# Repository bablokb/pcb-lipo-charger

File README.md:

A small LiPo Charger using the MCP73831 and the XB6166IS
========================================================

Here are the KiCAD (v6) design-files for a small LiPo charger.
The charger supports charging with an attached load.

The charging IC is the MCP73831T-2ACI/OT. For details, see the
schematic.

For battery protection, the XB6166IS from XySemi is used.
Overcurrent detection kicks in at about 900mA, so this is
not a charger for high loads.

The charge curve below shows both phases: constant current at
the beginning and constant voltage after reaching the cutoff
voltage. Charge termination is at 15mA.

Schematic
---------

Layout
------

3D-Views
--------

License
-------

[![CC BY-SA 4.0][cc-by-sa-shield]][cc-by-sa]

This work is licensed under a
[Creative Commons Attribution-ShareAlike 4.0 International
License][cc-by-sa].

[![CC BY-SA 4.0][cc-by-sa-image]][cc-by-sa]

[cc-by-sa]: http://creativecommons.org/licenses/by-sa/4.0/
[cc-by-sa-image]: https://licensebuttons.net/l/by-sa/4.0/88x31.png
[cc-by-sa-shield]:
https://img.shields.io/badge/License-CC%20BY--SA%204.0-lightgrey.svg

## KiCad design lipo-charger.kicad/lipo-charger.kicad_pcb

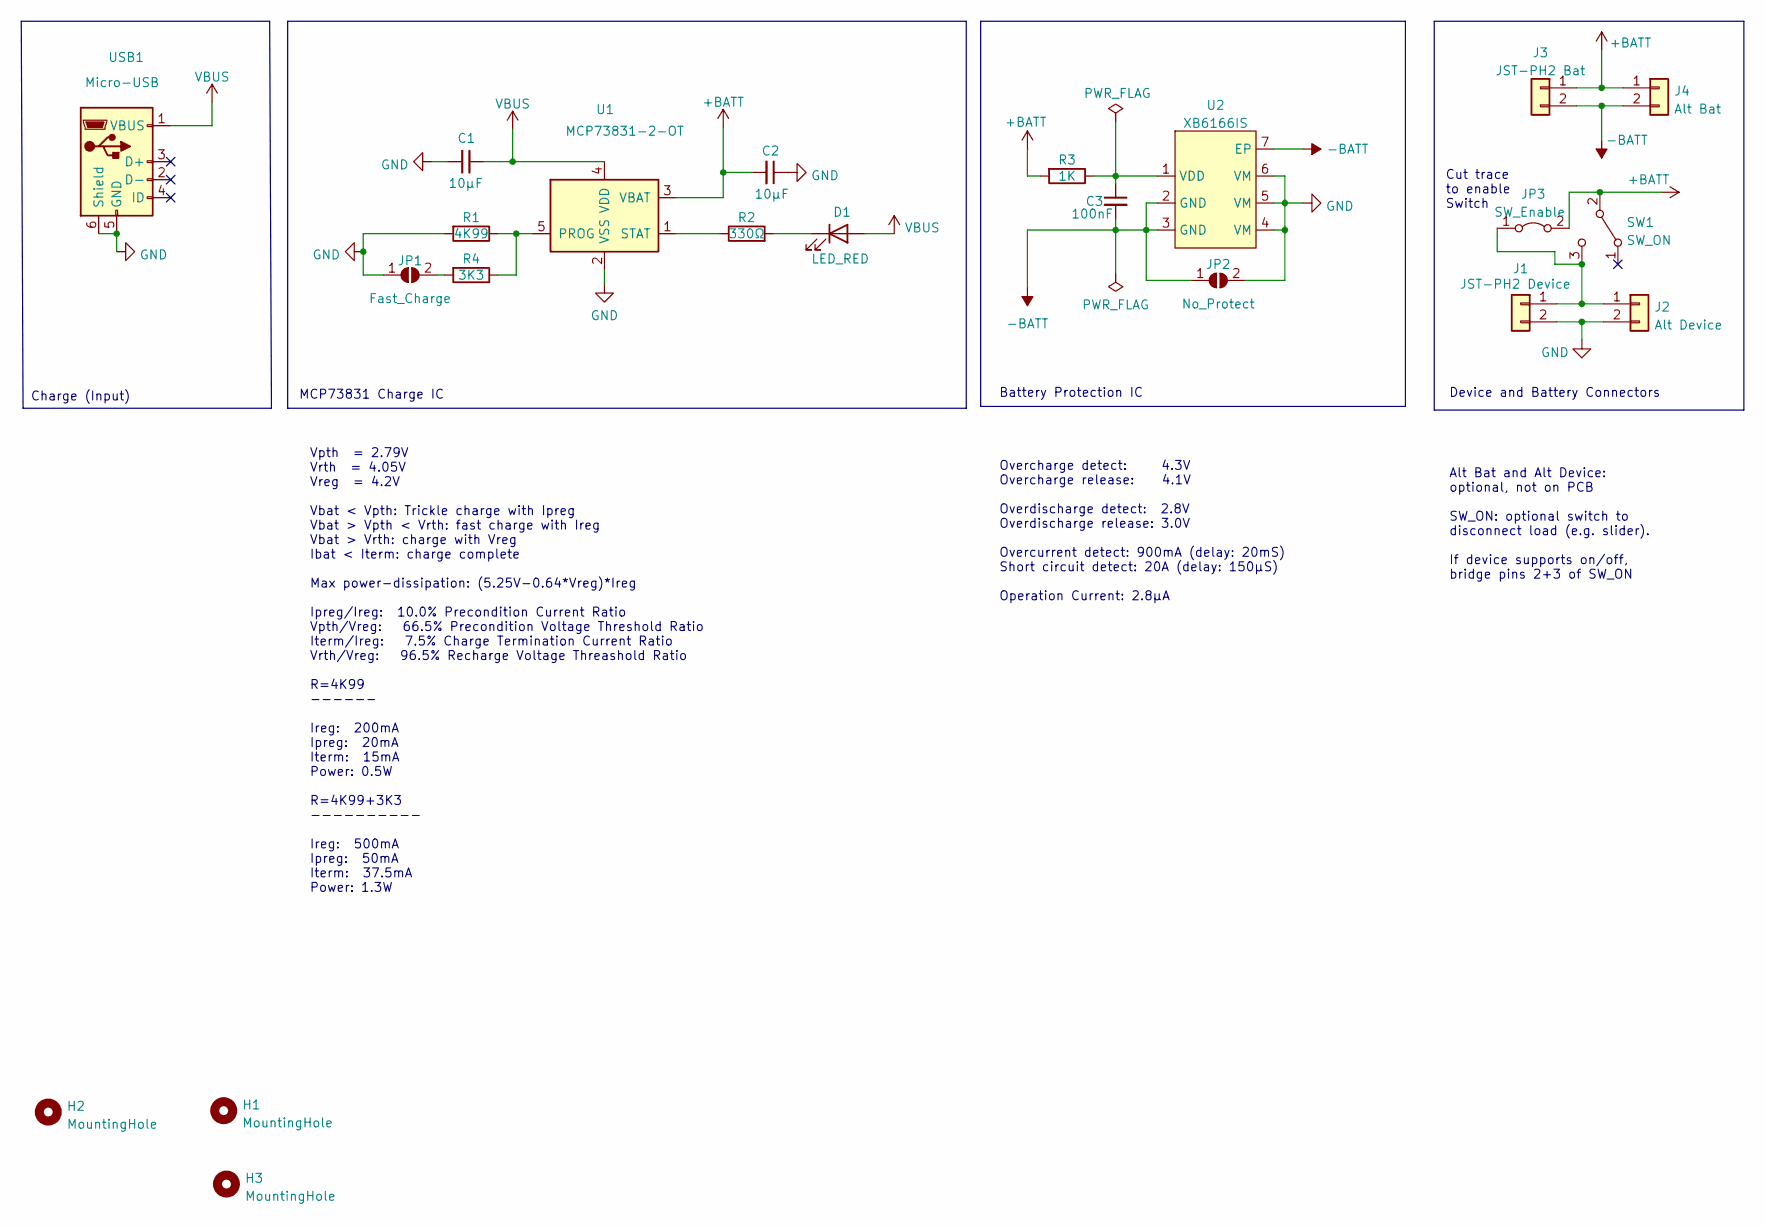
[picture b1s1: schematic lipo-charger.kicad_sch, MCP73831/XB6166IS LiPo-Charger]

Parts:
C1, C2: 10µF; C_0603_1608Metric; LCSC C19702
C3: 100nF; C_0402_1005Metric; LCSC C1525
D1: LED_RED; LED_0805_2012Metric; LCSC C84256
H1, H2, H3: MountingHole; MountingHole_2.4mm_M2
J1: JST-PH2 Device; JST_PH_S2B-PH-SM4-TB_1x02-1MP_P2.00mm_Horizontal; LCSC C295747
J2: Alt Device; PinHeader_1x02_P2.54mm_Vertical
J3: JST-PH2 Bat; JST_PH_S2B-PH-SM4-TB_1x02-1MP_P2.00mm_Horizontal; LCSC C295747
J4: Alt Bat; PinHeader_1x02_P2.54mm_Vertical
JP1: Fast_Charge; SolderJumper-2_P1.3mm_Open_Pad1.0x1.5mm
JP2: No_Protect; SolderJumper-2_P1.3mm_Open_Pad1.0x1.5mm
JP3: SW_Enable; SolderJumper-2_P1.3mm_Bridged_Pad1.0x1.5mm
R1: 4K99; R_0603_1608Metric; LCSC C23046
R2: 330Ω; R_0402_1005Metric; LCSC C25104
R3: 1K; R_0603_1608Metric; LCSC C21190
R4: 3K3; R_0603_1608Metric; LCSC C22978
SW1: SW_ON; PinHeader_1x03_P2.54mm_Vertical
U1: MCP73831-2-OT; SOT-23-5; LCSC C424093
U2: XB6166IS; DFN-2x2mm-0.75; LCSC C94310
USB1: Micro-USB; USB_Micro-B_JLCPCB_40942; LCSC C40942

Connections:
+BATT: C2.2, J3.1, J4.1, JP3.2 (B), R3.2, SW1.2 (B), U1.3 (VBAT)
-BATT: C3.2, J3.2, J4.2, JP2.1 (A), U2.2 (GND), U2.3 (GND), U2.7 (EP)
GND: C1.2, C2.1, J1.2, J2.2, JP1.1 (A), JP2.2 (B), R1.2, U1.2 (VSS), U2.4 (VM), U2.5 (VM), U2.6 (VM), USB1.5 (GND), USB1.6 (Shield)
unnamed: C3.1, R3.1, U2.1 (VDD)
unnamed: D1.1 (K), R2.2
unnamed: J1.1, J2.1, JP3.1 (A), SW1.3 (C)
unnamed: JP1.2 (B), R4.2
unnamed: R1.1, R4.1, U1.5 (PROG)
unnamed: R2.1, U1.1 (STAT)
VBUS: C1.1, D1.2 (A), U1.4 (VDD), USB1.1 (VBUS)

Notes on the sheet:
Vpth = 2.79V Vrth = 4.05V Vreg = 4.2V Vbat < Vpth: Trickle charge with Ipreg Vbat > Vpth < Vrth: fast charge with Ireg Vbat > Vrth: charge with Vreg Ibat < Iterm: charge complete Max power-dissipation: (5.25V-0.64*Vreg)*Ireg Ipreg/Ireg: 10.0% Precondition Current Ratio Vpth/Vreg: 66.5% Precondition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
Battery Protection IC
Overcharge detect: 4.3V Overcharge release: 4.1V Overdischarge detect: 2.8V Overdischarge release: 3.0V Overcurrent detect: 900mA (delay: 20mS) Short circuit detect: 20A (delay: 150µS) Operation Current: 2.8µA
Device and Battery Connectors
Alt Bat and Alt Device: optional, not on PCB SW_ON: optional switch to disconnect load (e.g. slider). If device supports on/off, bridge pins 2+3 of SW_ON
Charge (Input)
Cut trace to enable Switch
MCP73831 Charge IC

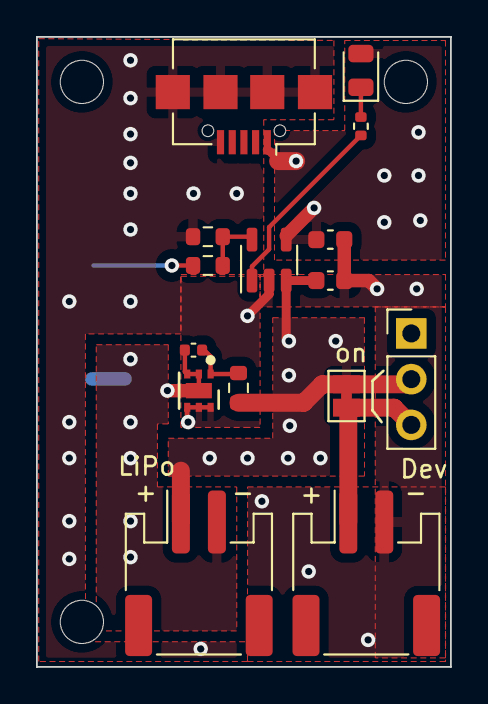
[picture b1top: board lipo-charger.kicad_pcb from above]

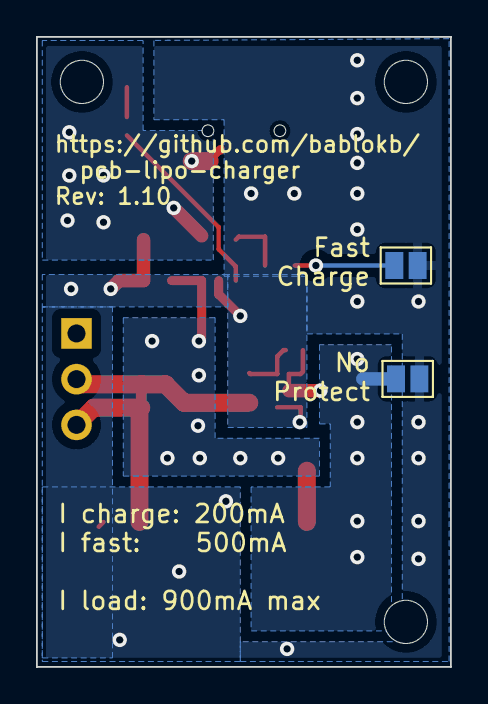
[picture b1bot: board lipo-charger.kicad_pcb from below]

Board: 2 copper layers, 23.0 x 35.0 mm, 20 parts (2 on the bottom side), 10 nets.

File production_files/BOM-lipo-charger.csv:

Comment,Designator,Footprint,LCSC
100nF,C3,C_0402_1005Metric,C1525
10µF,"C1,C2",C_0603_1608Metric,C19702
1K,R3,R_0603_1608Metric,C21190
3K3,R4,R_0603_1608Metric,C22978
4K99,R1,R_0603_1608Metric,C23046
330Ω,R2,R_0402_1005Metric,C25104
JST-PH2 Device,"J1,J3",JST_PH_S2B-PH-SM4-TB_1x02-1MP_P2.00mm_Horizontal,C295747
Micro-USB,USB1,USB_Micro-B_JLCPCB_40942,C40942
MCP73831-2-OT,U1,SOT-23-5,C424093
LED_RED,D1,LED_0805_2012Metric,C84256
XB6166IS,U2,DFN-2x2mm-0.75,C94310

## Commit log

2023-12-30 Rev 0.91: remove alternative connectors for LiPo and device
2023-12-30 Rev: 0.92: add (optional) switch for load
2024-01-02 Rev. 0.93 (added switch for load) - in production
2024-02-01 Rev 1.10: added 'always-on' trace-jumper
2024-02-01 added 3D-view from JLCPCB
2024-02-26 added charge curve
